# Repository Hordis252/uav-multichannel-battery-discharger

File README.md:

# Multi-Channel UAV Battery Discharger

> **Bakalářská práce:** Vícekanálová vybíječka akumulátorů pro bezpilotní letouny  
> **Pracoviště:** Skupina multirobotických systémů (MRS), FEL ČVUT v Praze  
> **Autor:** Adam Horák  
> **Vedoucí:** Tomáš Kestřánek

---

## 📌 O projektu
Cílem projektu je návrh, konstrukce a naprogramování inteligentního zařízení pro bezpečné a efektivní vybíjení sady akumulátorů do skladovacího (*storage*) napětí. Zařízení je optimalizováno pro laboratorní a terénní provoz bezpilotních letounů (UAV) skupiny MRS.

Klíčovou vlastností je plná automatizace – systém sám detekuje parametry připojených akumulátorů, spravuje frontu sekvenčního vybíjení a umožňuje vzájemné propojení více modulů pro sdílení zátěže (paralelní rozptyl výkonu do sousedního modulu).

### ⚙️ Klíčové technické parametry

| Parametr | Specifikace |
| :--- | :--- |
| **Podporovaná chemie** | Li-Po, Li-Ion |
| **Konfigurace článků** | 3S až 12S (napětí 10 V – 55 V) |
| **Kapacita portů** | 1 až 4 nezávislé baterie (výkonové XT60 / XT90) |
| **Vybíjecí výkon** | Min. 250 W (sekvenční vybíjení s prioritizací fronty) |
| **Řízení & automatizace** | Automatická detekce parametrů, plug & play storage režim |
| **Škálovatelnost** | Modulární propojení (sdílení zátěže mezi moduly) |
| **Bezpečnost** | HW i SW ochrany proti přebití/přehřátí, kompaktní kryt |

### 🎯 Rozšíření (volitelné cíle)
- [ ] Implementace pasivního balancování jednotlivých článků (BMS / balanční konektory)
- [ ] Doplňková funkce jednokanálového nabíjení

---

## 🖼️ Náhled hardwaru

### Přepínač kanálů ([hw/power-stage/](hw/power-stage/)) 

### Zátěž ([hw/load-board/](hw/load-board/))

### Ovládací panel ([hw/ui-control-board-side/](hw/ui-control-board-side/))

### Demultiplexor a CAN ([hw/mcu-board/](hw/mcu-board/))

---

## 📝 Aktuální stav
- [x] Návrh blokového schématu a rozdělení systému na funkční moduly (viz [náčrty v doc/sketches](doc/sketches/))
- [ ] Rozdělení na menší segmenty pro otestování - IN PROGRESS

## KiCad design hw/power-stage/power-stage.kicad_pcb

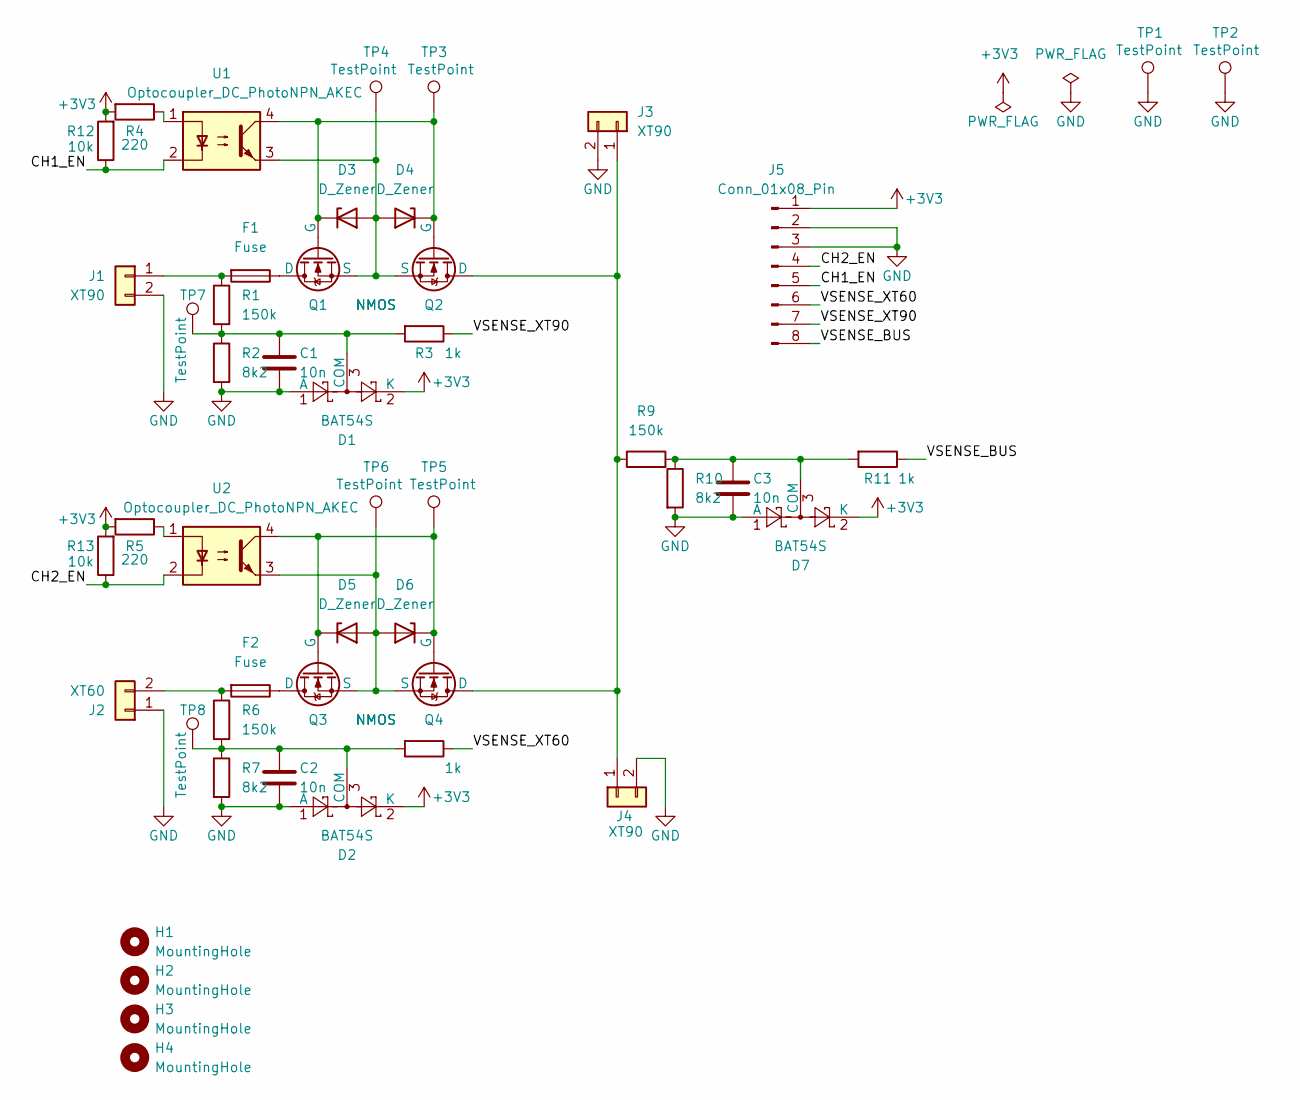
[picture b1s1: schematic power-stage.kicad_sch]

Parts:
C1, C2, C3: 10n; C_0805_2012Metric
D1, D2, D7: BAT54S; SOT-23
D3, D4, D5, D6: D_Zener; D_SOD-123
F1, F2: Fuse; 3557-2
H1, H2, H3, H4: MountingHole; MountingHole_3.2mm_M3
J1, J4: XT90; XT90PWM
J2: XT60; XT60PWM
J3: XT90; XT90PWF
J5: Conn_01x08_Pin; PinHeader_1x08_P2.54mm_Vertical
Q1, Q2, Q3, Q4: NMOS; IPB017N10N5ATMA1_pinout
R1, R6, R9: 150k; R_0805_2012Metric
R2, R7, R10: 8k2; R_0805_2012Metric
R3, R8, R11: 1k; R_0805_2012Metric
R4, R5: 220; R_0805_2012Metric
R12, R13: 10k; R_0805_2012Metric
TP1, TP2: TestPoint; TestPoint_THTPad_D2.0mm_Drill1.0mm
TP3, TP4, TP5, TP6, TP7, TP8: TestPoint; TestPoint_Pad_D1.5mm
U1, U2: Optocoupler_DC_PhotoNPN_AKEC; SOP254P675X240-4N

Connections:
+3V3: D1.2 (K), D2.2 (K), D7.2 (K), J5.1, R4.2, R5.2, R12.2, R13.2
/CH1_EN: J5.5, R12.1, U1.2
/CH2_EN: J5.4, R13.1, U2.2
/VSENSE_BUS: J5.8, R11.1
/VSENSE_XT60: J5.6, R8.1
/VSENSE_XT90: J5.7, R3.1
GND: C1.2, C2.2, C3.2, D1.1 (A), D2.1 (A), D7.1 (A), J1.2, J2.1, J3.2, J4.2, J5.2, J5.3, R2.2, R7.2, R10.2, TP1.1 (1_1), TP2.1 (1_1)
unnamed: C1.1, D1.3 (COM), R1.2, R2.1, R3.2, TP7.1 (1_1)
unnamed: C2.1, D2.3 (COM), R6.2, R7.1, R8.2, TP8.1 (1_1)
unnamed: D3.2 (A), D4.2 (A), Q1.3 (S), Q2.3 (S), TP4.1 (1_1), U1.3
unnamed: D3.1 (K), D4.1 (K), Q1.2 (G), Q2.2 (G), TP3.1 (1_1), U1.4
unnamed: D5.2 (A), D6.2 (A), Q3.3 (S), Q4.3 (S), TP6.1 (1_1), U2.3
unnamed: D5.1 (K), D6.1 (K), Q3.2 (G), Q4.2 (G), TP5.1 (1_1), U2.4
unnamed: C3.1, D7.3 (COM), R9.2, R10.1, R11.2
unnamed: F1.2, J1.1, R1.1
unnamed: F2.2, J2.2, R6.1
unnamed: J3.1, J4.1, Q2.1 (D), Q4.1 (D), R9.1
unnamed: F1.1, Q1.1 (D)
unnamed: F2.1, Q3.1 (D)
unnamed: R4.1, U1.1
unnamed: R5.1, U2.1

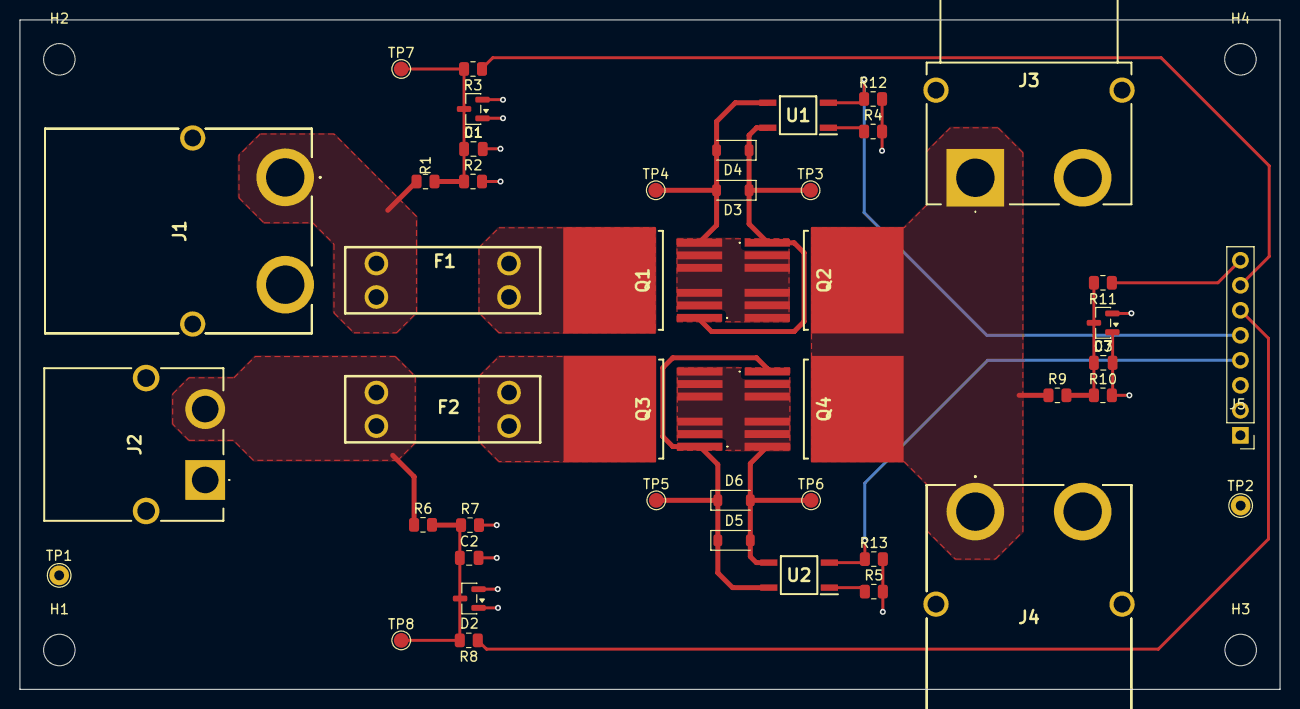
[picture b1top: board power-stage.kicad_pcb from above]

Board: 4 copper layers, 128.0 x 68.0 mm, 48 parts (0 on the bottom side), 21 nets.

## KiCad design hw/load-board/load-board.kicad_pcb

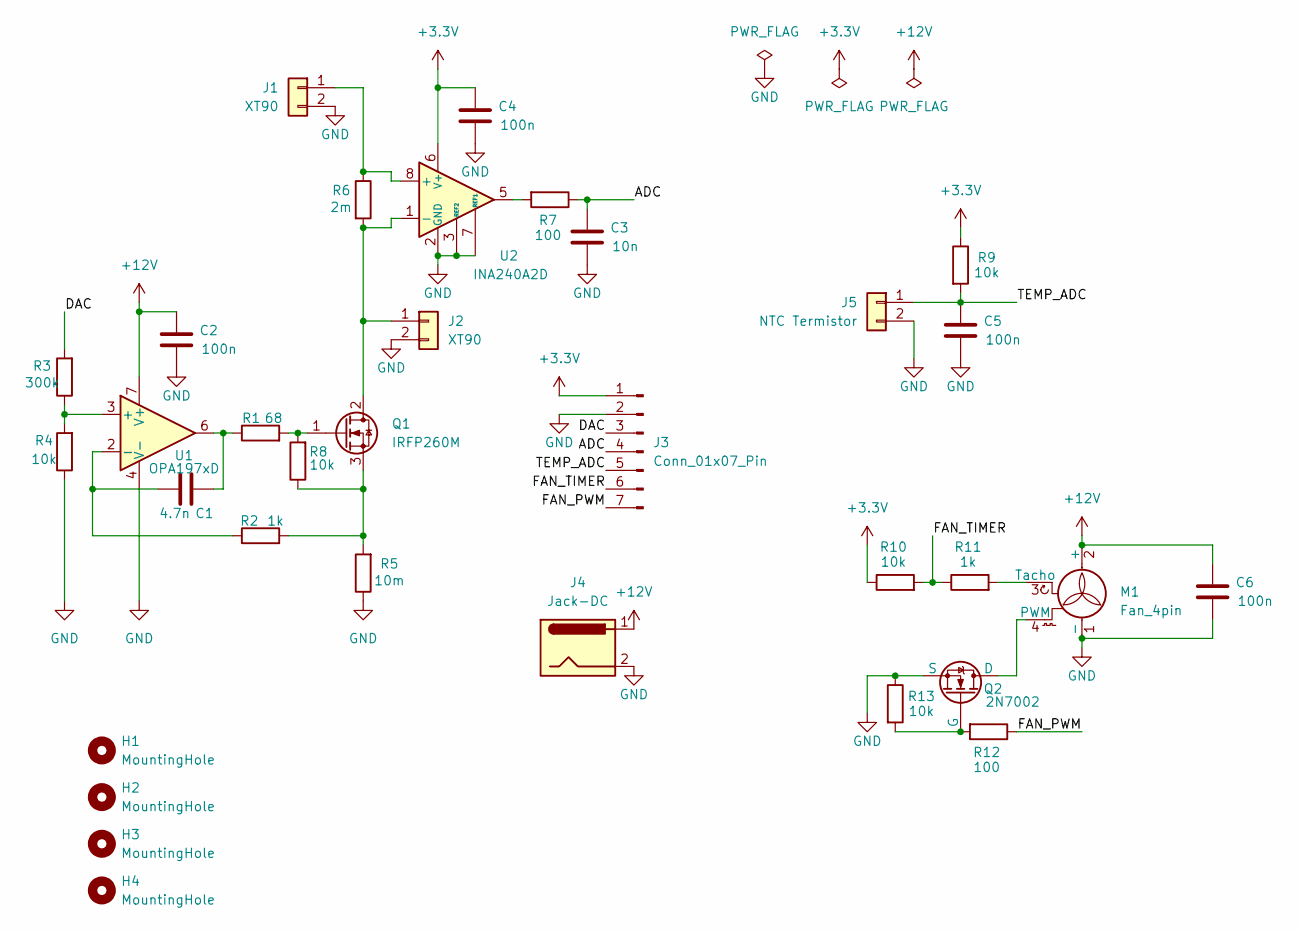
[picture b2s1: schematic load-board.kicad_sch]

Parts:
C1: 4.7n; C_0805_2012Metric
C2, C4, C5, C6: 100n; C_0805_2012Metric
C3: 10n; C_0805_2012Metric
H1, H2, H3, H4: MountingHole; MountingHole_3.2mm_M3
J1: XT90; XT90PWF
J2: XT90; XT90PWM
J3: Conn_01x07_Pin; PinHeader_1x07_P2.54mm_Vertical
J4: Jack-DC; BarrelJack_CUI_PJ-102AH_Horizontal
J5: NTC Termistor; PinHeader_1x02_P2.54mm_Vertical
M1: Fan_4pin; PinHeader_1x04_P2.54mm_Vertical
Q1: IRFP260M; TO-247-3_Vertical
Q2: 2N7002; TSOT-23
R1: 68; R_0805_2012Metric
R2, R11: 1k; R_0805_2012Metric
R3: 300k; R_0805_2012Metric
R4, R8, R9, R10, R13: 10k; R_0805_2012Metric
R5: 10m; R_2512_6332Metric
R6: 2m; R_2512_6332Metric
R7, R12: 100; R_0805_2012Metric
U1: OPA197xD; SOIC-8_3.9x4.9mm_P1.27mm
U2: INA240A2D; SOIC-8_3.9x4.9mm_P1.27mm

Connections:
+3.3V: C4.1, J3.1, R9.1, R10.1, U2.6 (V+)
+12V: C2.1, C6.1, J4.1, M1.2 (+), U1.7 (V+)
/ADC: C3.1, J3.4, R7.1
/DAC: J3.3, R3.2
/FAN_PWM: J3.7, R12.1
/FAN_TIMER: J3.6, R10.2, R11.1
/TEMP_ADC: C5.1, J3.5, J5.1, R9.2
GND: C2.2, C3.2, C4.2, C5.2, C6.2, J1.2, J2.2, J3.2, J4.2, J5.2, M1.1 (-), Q2.3 (S), R4.1, R5.1, R13.1, U1.4 (V-), U2.2 (GND), U2.3 (REF2), U2.4 (GND), U2.7 (REF1)
unnamed: C1.1, R1.1, U1.6
unnamed: J1.1, R6.1, U2.8 (+)
unnamed: J2.1, Q1.2 (D), R6.2, U2.1 (-)
unnamed: M1.4 (PWM), Q2.1 (D)
unnamed: M1.3 (Tacho), R11.2
unnamed: Q1.1 (G), R1.2, R8.2
unnamed: Q1.3 (S), R2.2, R5.2, R8.1
unnamed: Q2.2 (G), R12.2, R13.2
unnamed: R7.2, U2.5
unnamed: R3.1, R4.2, U1.3 (+)
unnamed: C1.2, R2.1, U1.2 (-)

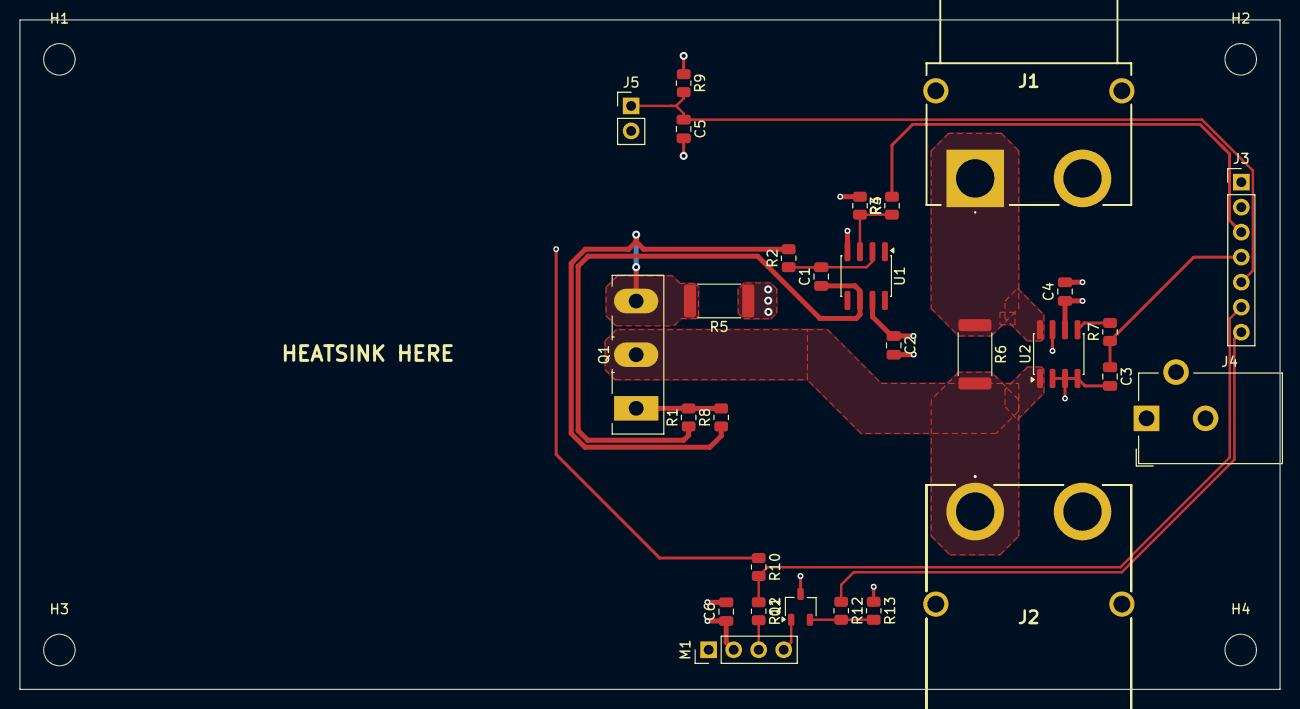
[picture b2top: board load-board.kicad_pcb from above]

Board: 4 copper layers, 128.0 x 68.0 mm, 33 parts (0 on the bottom side), 19 nets.

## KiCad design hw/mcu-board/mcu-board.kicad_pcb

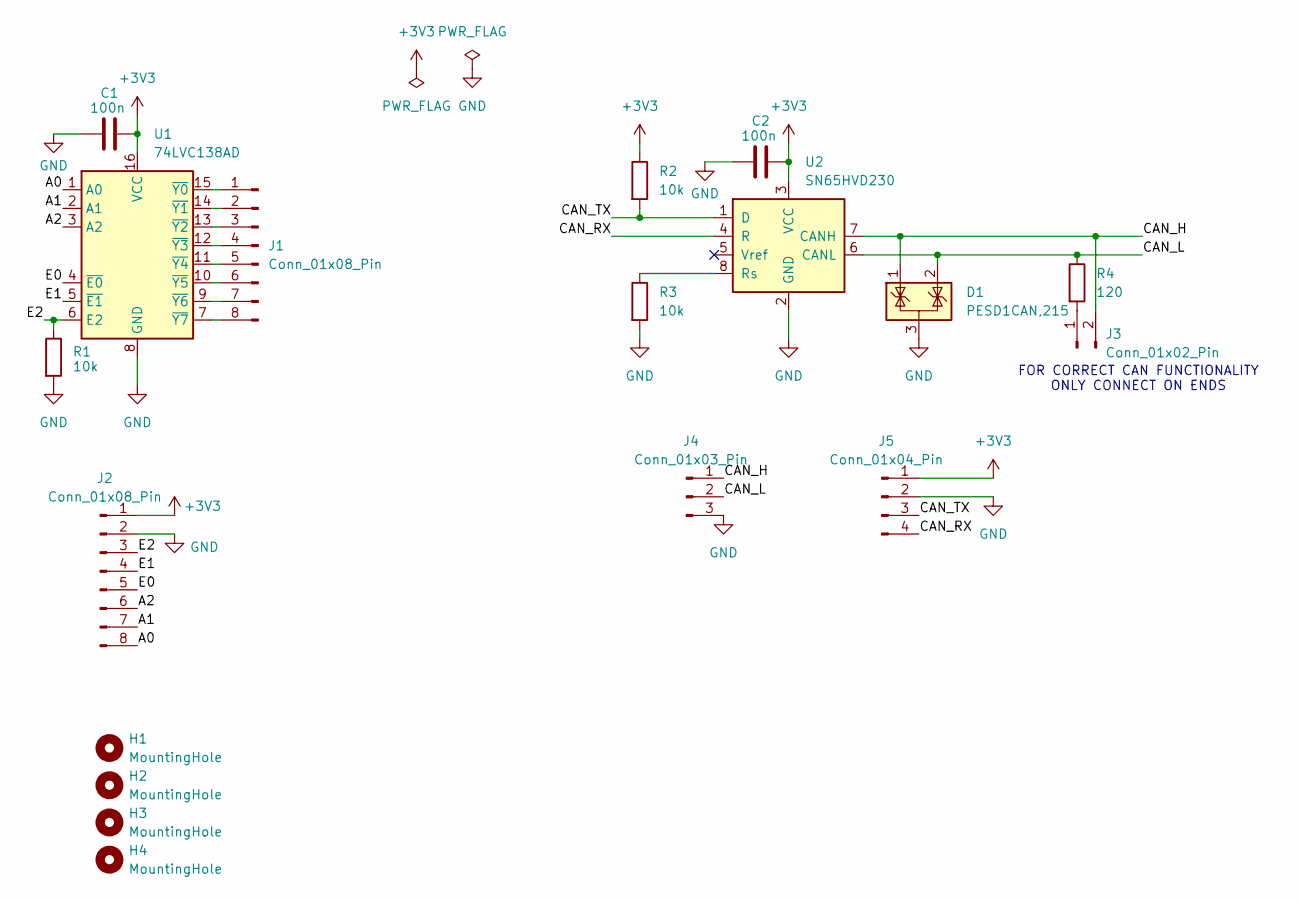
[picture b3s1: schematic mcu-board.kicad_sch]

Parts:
C1, C2: 100n; C_0805_2012Metric
D1: PESD1CAN,215; SOT-23
H1, H2, H3, H4: MountingHole; MountingHole_3.2mm_M3
J1, J2: Conn_01x08_Pin; PinHeader_1x08_P2.54mm_Vertical
J3: Conn_01x02_Pin; PinHeader_1x02_P2.54mm_Vertical
J4: Conn_01x03_Pin; PinHeader_1x03_P2.54mm_Vertical
J5: Conn_01x04_Pin; PinHeader_1x04_P2.54mm_Vertical
R1, R2, R3: 10k; R_0805_2012Metric
R4: 120; R_0805_2012Metric
U1: 74LVC138AD; SOIC-16_3.9x9.9mm_P1.27mm
U2: SN65HVD230; SOIC-8_3.9x4.9mm_P1.27mm

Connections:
+3V3: C1.1, C2.1, J2.1, J5.1, R2.1, U1.16 (VCC), U2.3 (VCC)
/A0: J2.8, U1.1 (A0)
/A1: J2.7, U1.2 (A1)
/A2: J2.6, U1.3 (A2)
/CAN_H: D1.1 (K), J3.2, J4.1, U2.7 (CANH)
/CAN_L: D1.2 (K), J4.2, R4.1, U2.6 (CANL)
/CAN_RX: J5.4, U2.4 (R)
/CAN_TX: J5.3, R2.2, U2.1 (D)
/E0: J2.5, U1.4 (~E0)
/E1: J2.4, U1.5 (~E1)
/E2: J2.3, R1.1, U1.6 (E2)
GND: C1.2, C2.2, D1.3 (A), J2.2, J4.3, J5.2, R1.2, R3.2, U1.8 (GND), U2.2 (GND)
unnamed: J1.1, U1.15 (~Y0)
unnamed: J1.2, U1.14 (~Y1)
unnamed: J1.3, U1.13 (~Y2)
unnamed: J1.4, U1.12 (~Y3)
unnamed: J1.5, U1.11 (~Y4)
unnamed: J1.6, U1.10 (~Y5)
unnamed: J1.7, U1.9 (~Y6)
unnamed: J1.8, U1.7 (~Y7)
unnamed: J3.1, R4.2
unnamed: R3.1, U2.8 (Rs)

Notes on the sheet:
FOR CORRECT CAN FUNCTIONALITY ONLY CONNECT ON ENDS

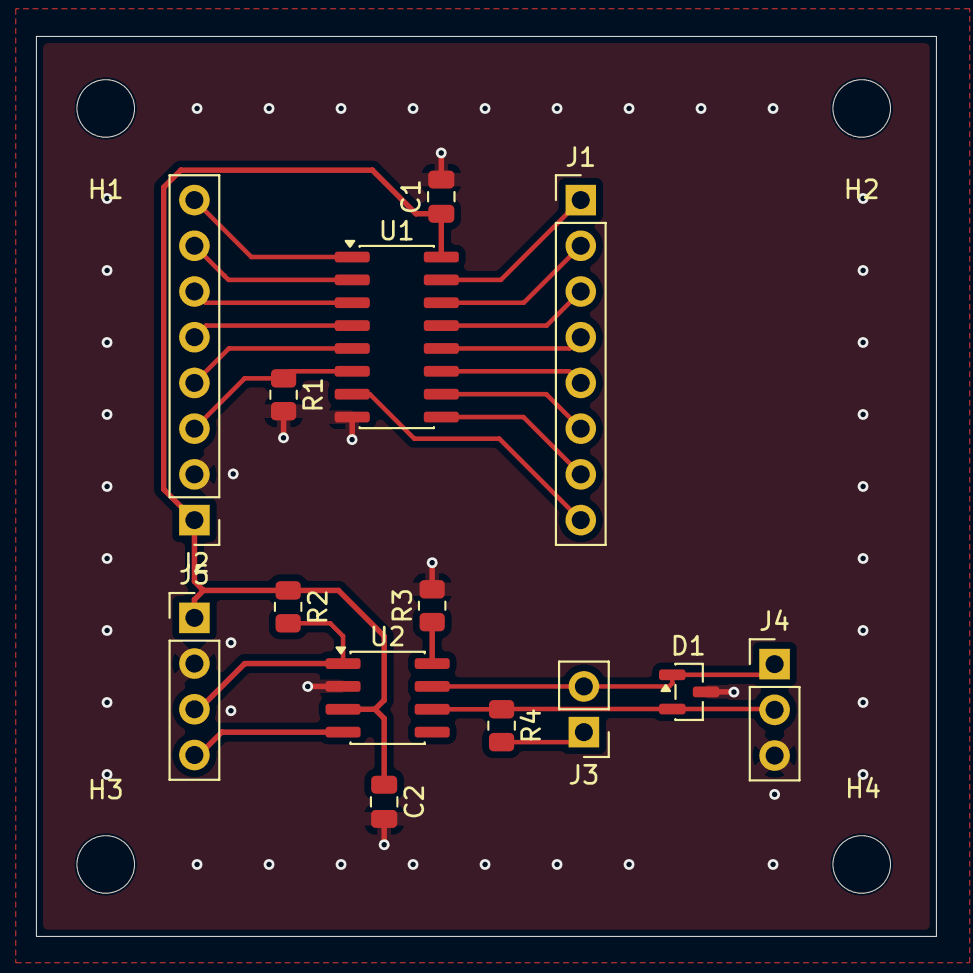
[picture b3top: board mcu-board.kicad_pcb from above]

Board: 2 copper layers, 50.0 x 50.0 mm, 18 parts (0 on the bottom side), 22 nets.

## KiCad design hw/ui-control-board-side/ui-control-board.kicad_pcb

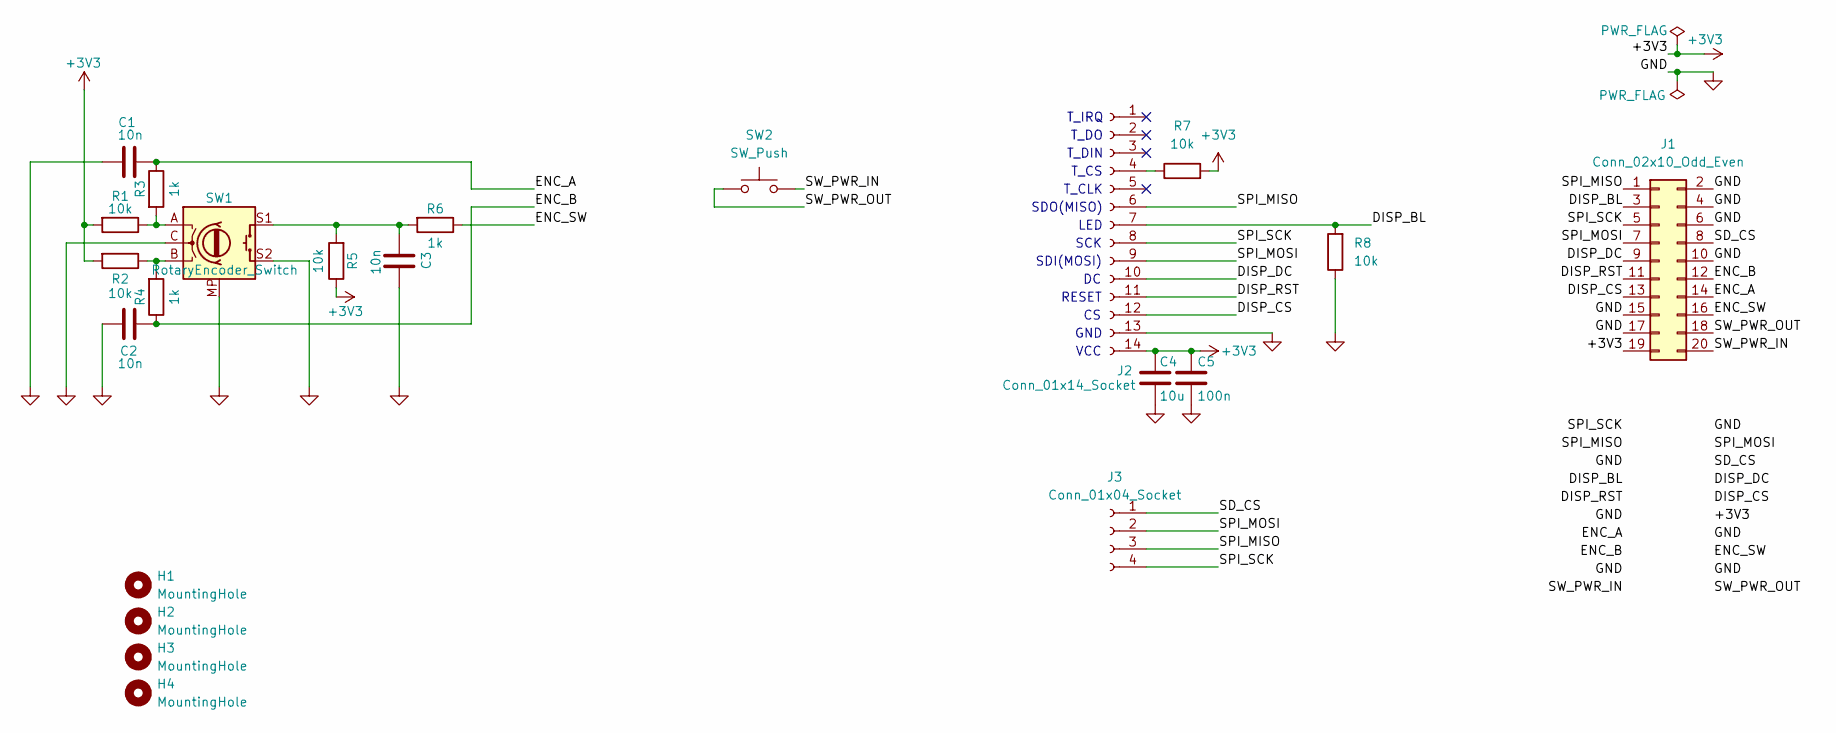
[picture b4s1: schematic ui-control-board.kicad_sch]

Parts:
C1, C2, C3: 10n; C_0805_2012Metric
C4: 10u; C_0805_2012Metric
C5: 100n; C_0805_2012Metric
H1, H2, H3, H4: MountingHole; MountingHole_3.2mm_M3
J1: Conn_02x10_Odd_Even; IDC-Header_2x10_P2.54mm_Horizontal
J2: Conn_01x14_Socket; PinHeader_1x14_P2.54mm_Vertical
J3: Conn_01x04_Socket; PinHeader_1x04_P2.54mm_Vertical
R1, R2, R5, R7, R8: 10k; R_0805_2012Metric
R3, R4, R6: 1k; R_0805_2012Metric
SW1: RotaryEncoder_Switch; RotaryEncoder_Alps_EC11E-Switch_Vertical_H20mm
SW2: SW_Push; SW_PUSH_6mm

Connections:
+3V3: C4.1, C5.1, J1.19, J2.14, R1.2, R2.2, R5.1, R7.2
/DISP_BL: J1.3, J2.7, R8.2
/DISP_CS: J1.13, J2.12
/DISP_DC: J1.9, J2.10
/DISP_RST: J1.11, J2.11
/ENC_A: C1.2, J1.14, R3.1
/ENC_B: C2.2, J1.12, R4.1
/ENC_SW: J1.16, R6.1
/SD_CS: J1.8, J3.1
/SPI_MISO: J1.1, J2.6, J3.3
/SPI_MOSI: J1.7, J2.9, J3.2
/SPI_SCK: J1.5, J2.8, J3.4
/SW_PWR_IN: J1.20, SW2.2
/SW_PWR_OUT: J1.18, SW2.1
GND: C1.1, C2.1, C3.1, C4.2, C5.2, J1.2, J1.4, J1.6, J1.10, J1.15, J1.17, J2.13, R8.1, SW1.C, SW1.MP, SW1.S2
unnamed: C3.2, R5.2, R6.2, SW1.S1
unnamed: J2.4, R7.1
unnamed: R1.1, R3.2, SW1.A
unnamed: R2.1, R4.2, SW1.B

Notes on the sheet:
T_DO
RESET
VCC
T_CS
GND
SDO(MISO)
SDI(MOSI)
T_CLK
LED
SCK
T_DIN
T_IRQ

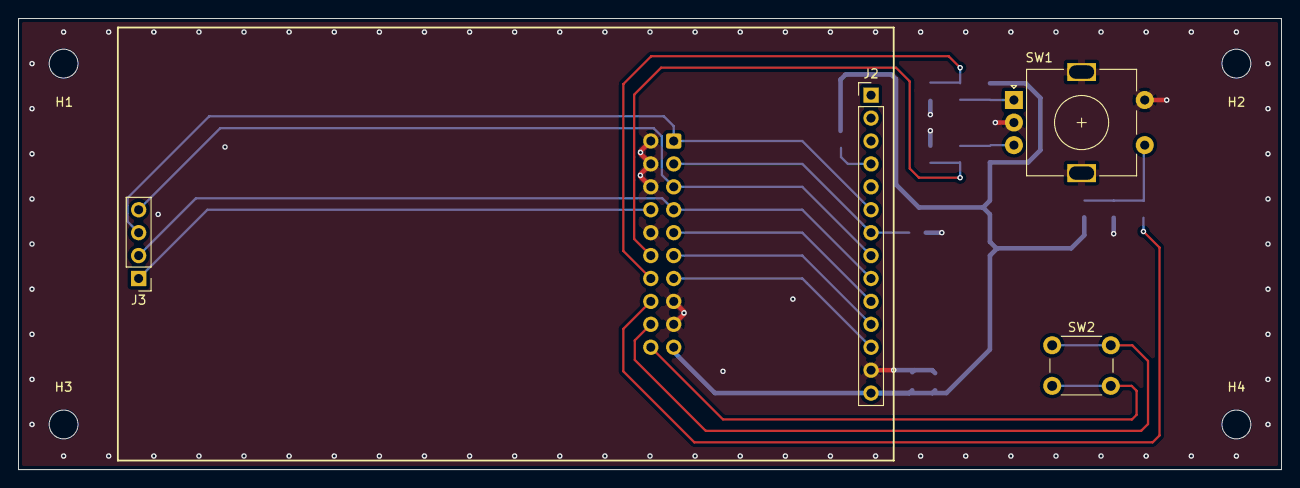
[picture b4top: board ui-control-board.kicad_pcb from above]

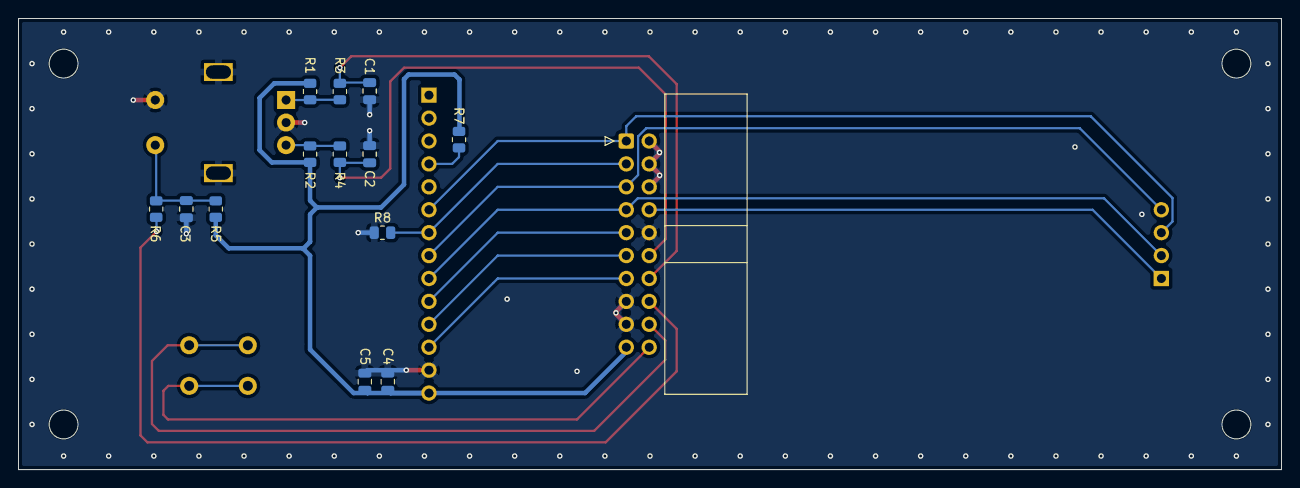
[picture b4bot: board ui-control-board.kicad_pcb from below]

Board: 2 copper layers, 140.0 x 50.0 mm, 22 parts (14 on the bottom side), 19 nets.
